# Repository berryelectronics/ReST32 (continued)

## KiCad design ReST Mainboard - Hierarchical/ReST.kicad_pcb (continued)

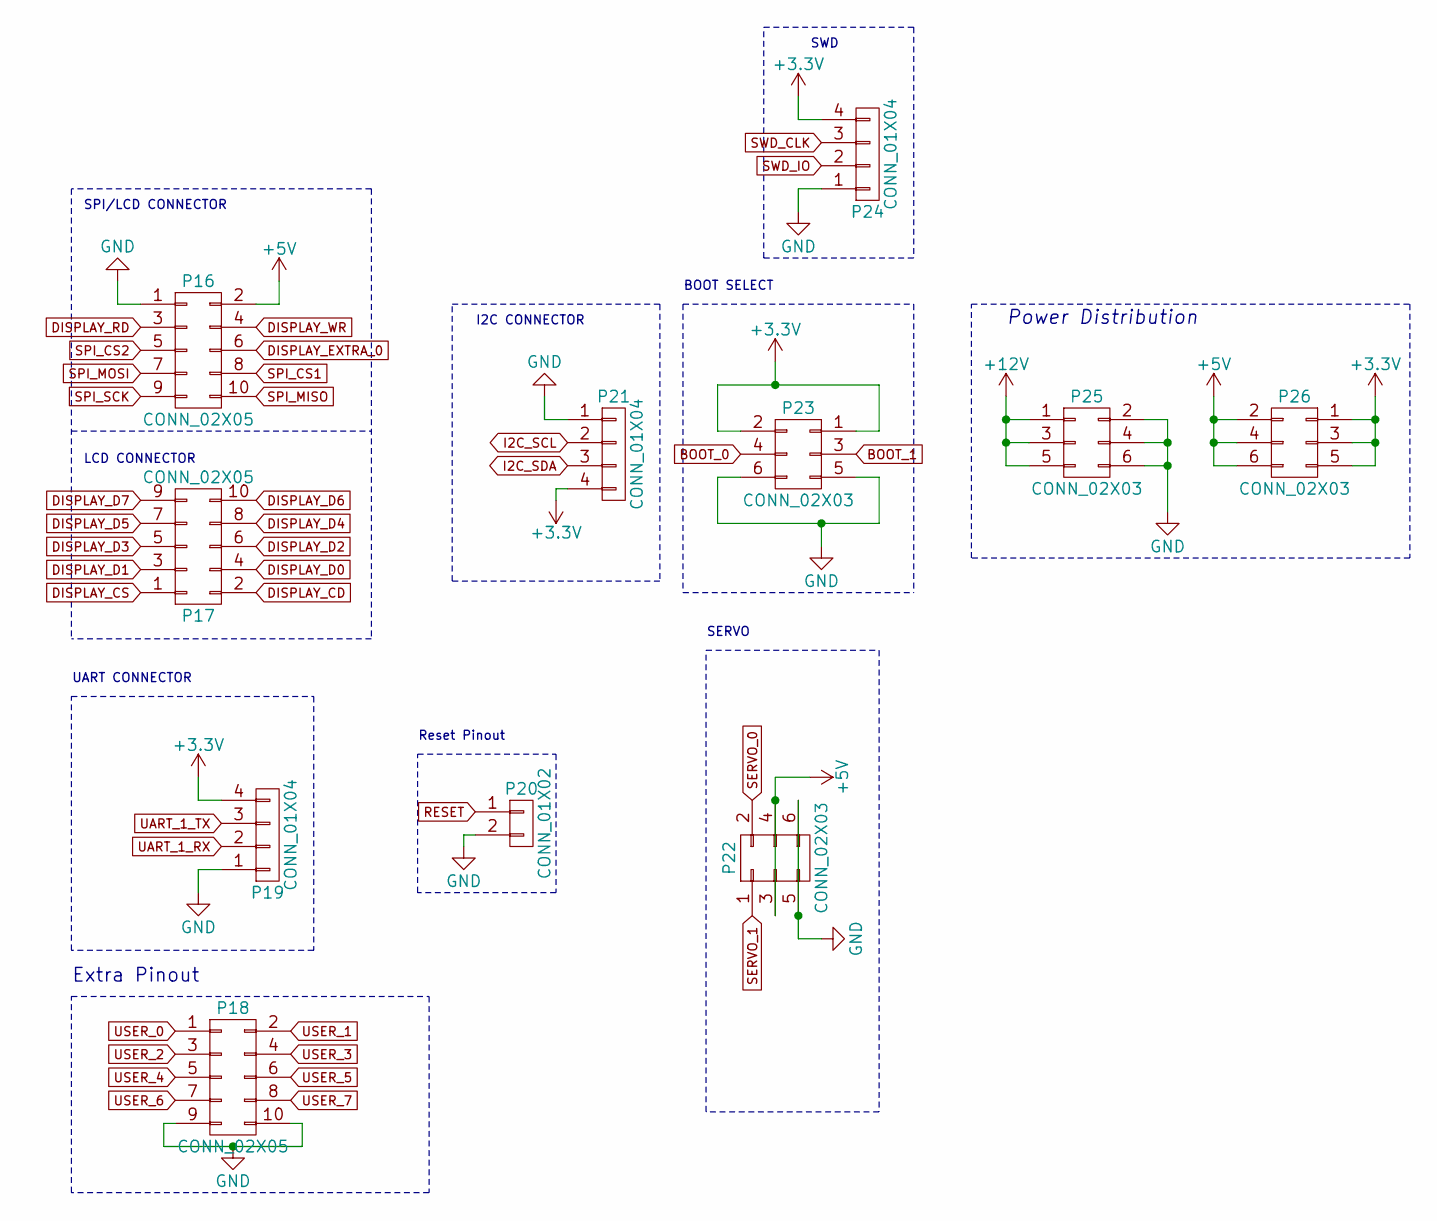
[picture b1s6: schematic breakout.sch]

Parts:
P16, P17: CONN_02X05; IDC_Header_Straight_10pins
P18: CONN_02X05; Pin_Header_Straight_2x05
P19, P24: CONN_01X04; bb02-hy04a
P20: CONN_01X02; Pin_Header_Straight_1x02
P21: CONN_01X04; Pin_Header_Straight_1x04
P22, P23: CONN_02X03; bb02-hp06
P25, P26: CONN_02X03; Pin_Header_Straight_2x03

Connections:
+5V: P16.2, P22.3, P22.4, P26.2, P26.4, P26.6; also elsewhere on the board
+12V: P25.1, P25.3, P25.5; also elsewhere on the board
BOOT_0: P23.4; also elsewhere on the board
BOOT_1: P23.3; also elsewhere on the board
DISPLAY_CD: P17.2; also elsewhere on the board
DISPLAY_CS: P17.1; also elsewhere on the board
DISPLAY_D0: P17.4; also elsewhere on the board
DISPLAY_D1: P17.3; also elsewhere on the board
DISPLAY_D2: P17.6; also elsewhere on the board
DISPLAY_D3: P17.5; also elsewhere on the board
DISPLAY_D4: P17.8; also elsewhere on the board
DISPLAY_D5: P17.7; also elsewhere on the board
DISPLAY_D6: P17.10; also elsewhere on the board
DISPLAY_D7: P17.9; also elsewhere on the board
DISPLAY_EXTRA_0: P16.6; also elsewhere on the board
DISPLAY_RD: P16.3; also elsewhere on the board
DISPLAY_WR: P16.4; also elsewhere on the board
GND: P16.1, P18.9, P18.10, P19.1, P20.2, P21.1, P22.5, P22.6, P23.5, P23.6, P24.1, P25.2, P25.4, P25.6; also elsewhere on the board
I2C_SCL: P21.2; also elsewhere on the board
I2C_SDA: P21.3; also elsewhere on the board
RESET: P20.1; also elsewhere on the board
SERVO_0: P22.2; also elsewhere on the board
SERVO_1: P22.1; also elsewhere on the board
SPI_CS1: P16.8; also elsewhere on the board
SPI_CS2: P16.5; also elsewhere on the board
SPI_MISO: P16.10; also elsewhere on the board
SPI_MOSI: P16.7; also elsewhere on the board
SPI_SCK: P16.9; also elsewhere on the board
SWD_CLK: P24.3; also elsewhere on the board
SWD_IO: P24.2; also elsewhere on the board
UART_1_RX: P19.2; also elsewhere on the board
UART_1_TX: P19.3; also elsewhere on the board
USER_0: P18.1; also elsewhere on the board
USER_1: P18.2; also elsewhere on the board
USER_2: P18.3; also elsewhere on the board
USER_3: P18.4; also elsewhere on the board
USER_4: P18.5; also elsewhere on the board
USER_5: P18.6; also elsewhere on the board
USER_6: P18.7; also elsewhere on the board
USER_7: P18.8; also elsewhere on the board

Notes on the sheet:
Power Distribution
SPI/LCD CONNECTOR
BOOT SELECT
I2C CONNECTOR
SERVO
UART CONNECTOR
SWD
LCD CONNECTOR
Extra Pinout
Reset Pinout

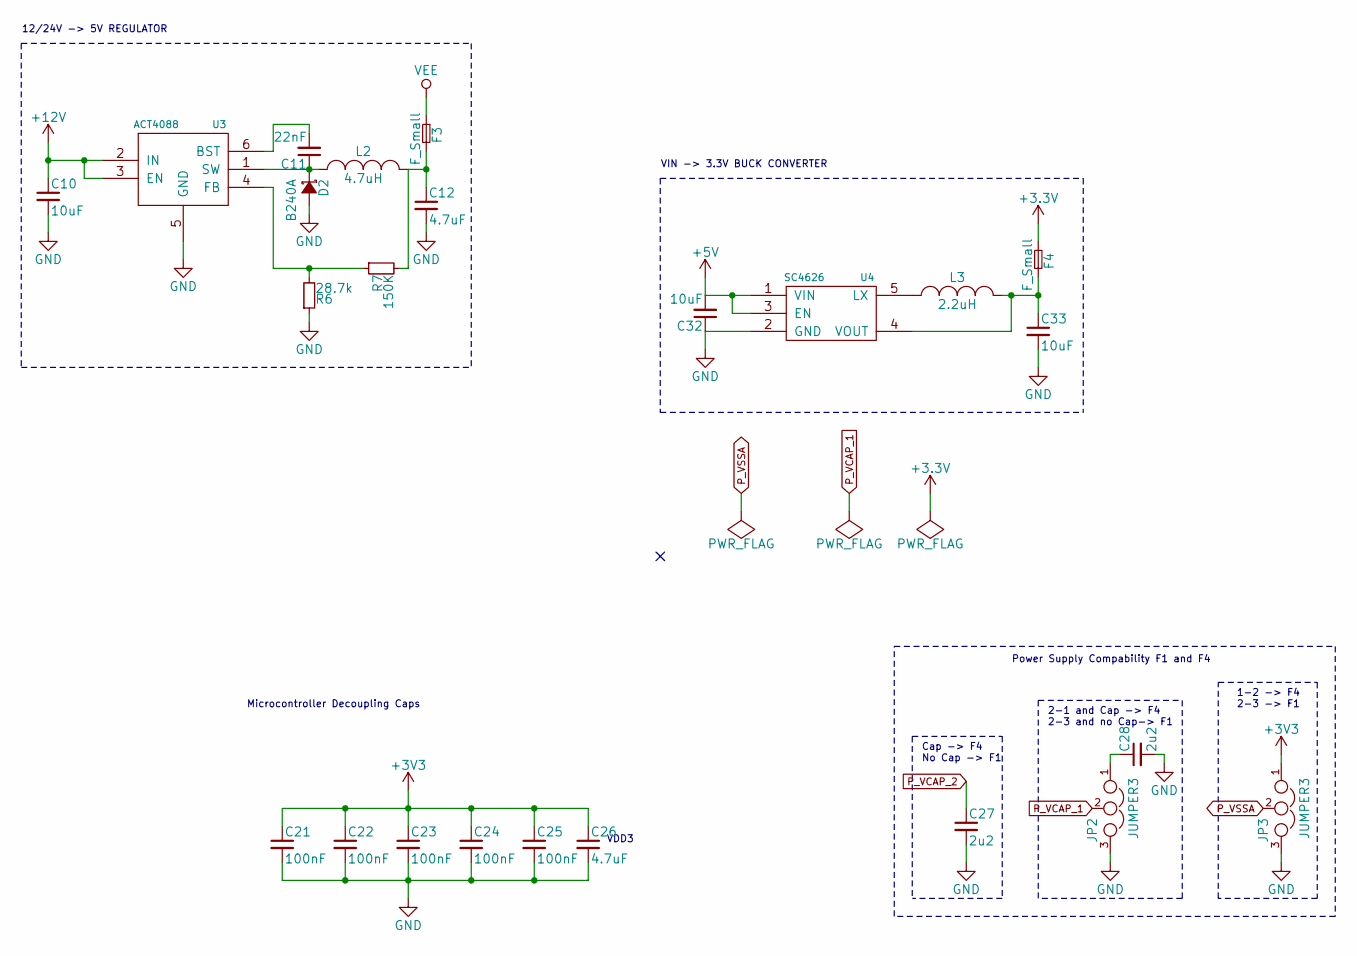
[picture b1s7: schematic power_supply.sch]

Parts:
C10: 10uF; C_1206_HandSoldering
C11: 22nF; C_0805_HandSoldering
C12, C26: 4.7uF; C_0805_HandSoldering
C21, C22, C23, C24, C25: 100nF; C_0805_HandSoldering
C27, C28: 2u2; C_0805_HandSoldering
C32, C33: 10uF; C_0805_HandSoldering
D2: B240A; DO-214AC.SMA
F3: F_Small; FUSE-1812
F4: F_Small; R_0805_HandSoldering
JP2, JP3: JUMPER3; S_JUMPER_3
L2: 4.7uH; CD32
L3: 2.2uH; CD32
R6: 28.7k; R_0805_HandSoldering
R7: 150K; R_0805_HandSoldering
U3: ACT4088; SOT-23-6
U4: SC4626; SOT-23-5

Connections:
+5V: C32.2, U4.1 (VIN), U4.3 (EN); also elsewhere on the board
+12V: C10.1, U3.2 (IN), U3.3 (EN); also elsewhere on the board
GND: C10.2, C12.2, C21.2, C22.2, C23.2, C24.2, C25.2, C26.2, C27.2, C28.2, C32.1, C33.2, D2.2 (A), JP2.3, JP3.3, R6.1, U3.5 (GND), U4.2 (GND); also elsewhere on the board
unnamed: C11.1, D2.1 (K), L2.1, U3.1 (SW)
unnamed: C11.2, U3.6 (BST)
unnamed: C12.1, F3.2, L2.2, R7.2
unnamed: C28.1, JP2.1
unnamed: C33.1, F4.2, L3.2, U4.4 (VOUT)
unnamed: L3.1, U4.5 (LX)
unnamed: R6.2, R7.1, U3.4 (FB)
P_VCAP_1: JP2.2; also elsewhere on the board
P_VCAP_2: C27.1; also elsewhere on the board
P_VSSA: JP3.2; also elsewhere on the board
VEE: F3.1; also elsewhere on the board

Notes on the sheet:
VIN -> 3.3V BUCK CONVERTER
12/24V -> 5V REGULATOR
2-1 and Cap -> F4 2-3 and no Cap-> F1
Cap -> F4 No Cap -> F1
1-2 -> F4 2-3 -> F1
Power Supply Compability F1 and F4
VDD3
Microcontroller Decoupling Caps

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
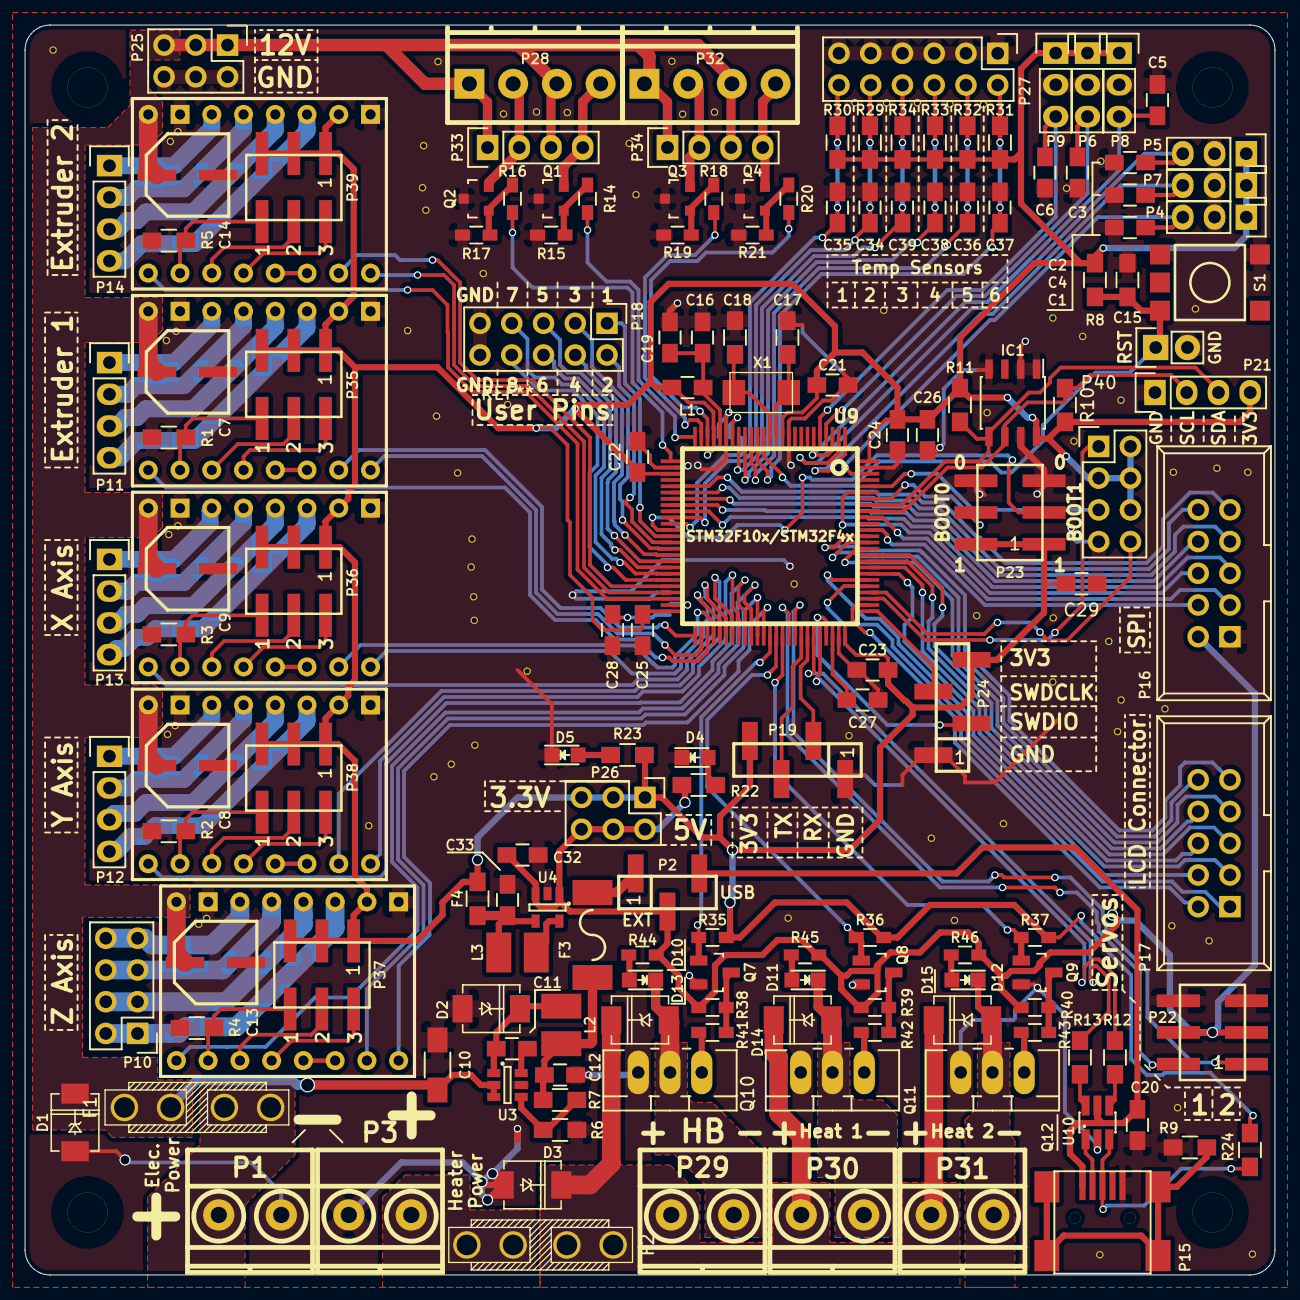
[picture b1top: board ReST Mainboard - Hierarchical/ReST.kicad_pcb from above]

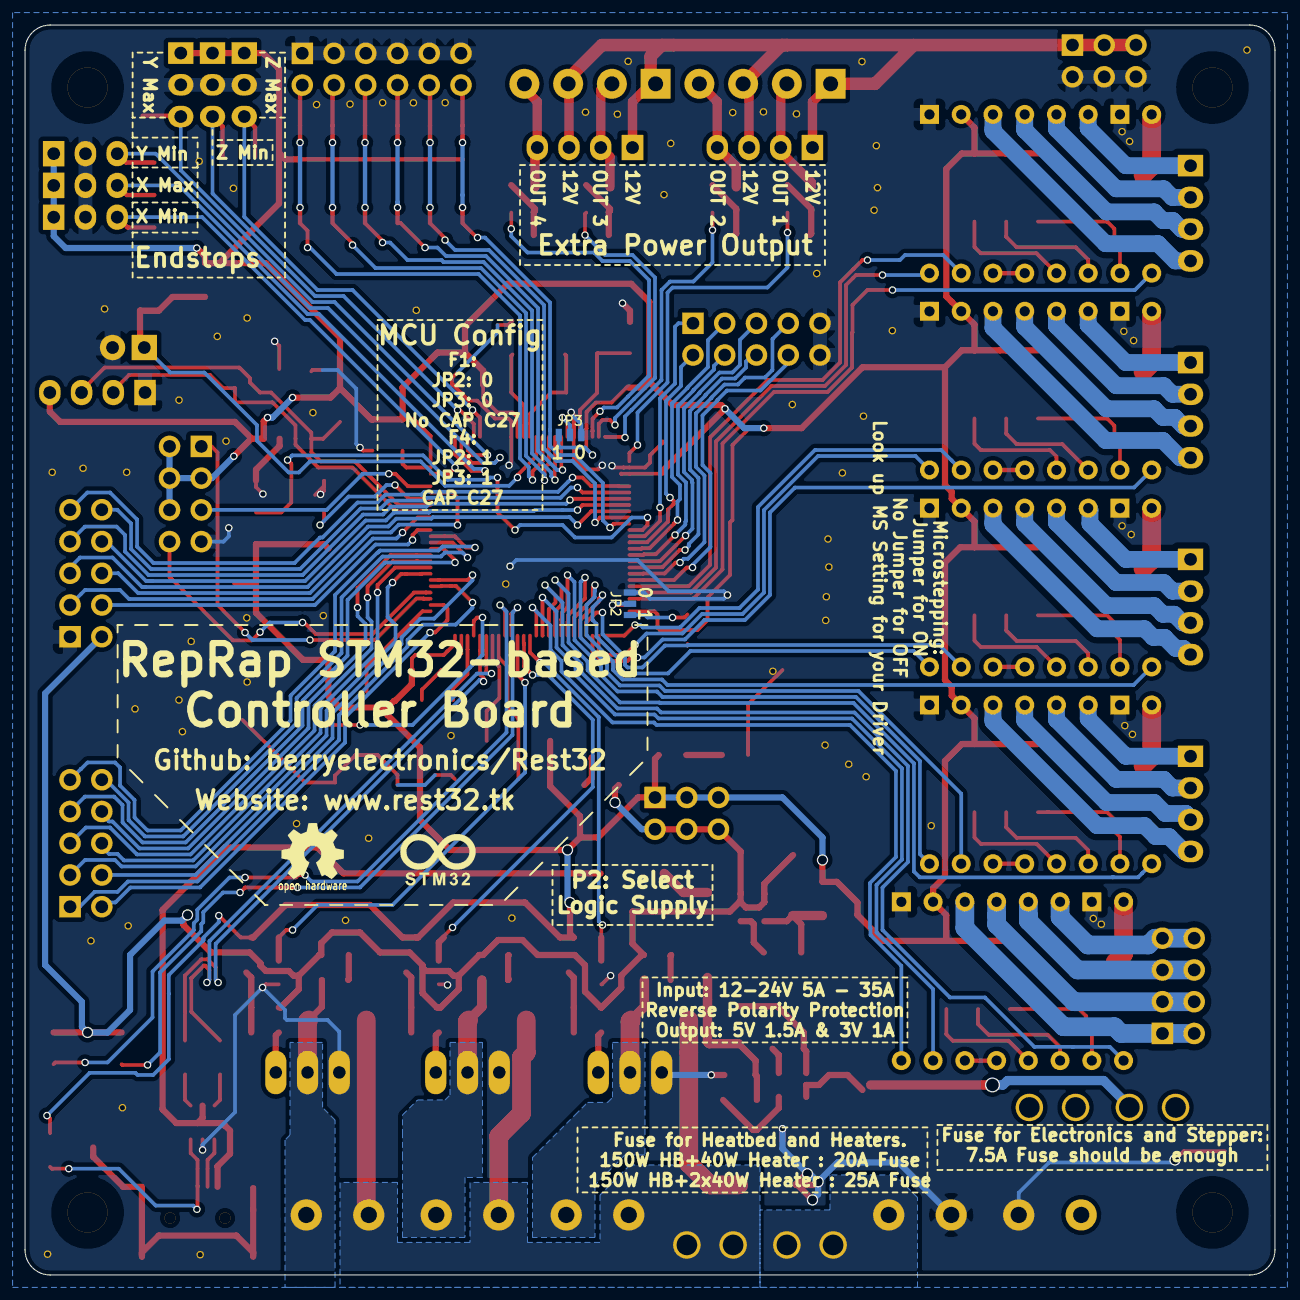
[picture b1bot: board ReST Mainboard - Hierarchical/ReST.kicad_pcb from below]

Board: 2 copper layers, 100.0 x 100.0 mm, 161 parts (2 on the bottom side), 165 nets.

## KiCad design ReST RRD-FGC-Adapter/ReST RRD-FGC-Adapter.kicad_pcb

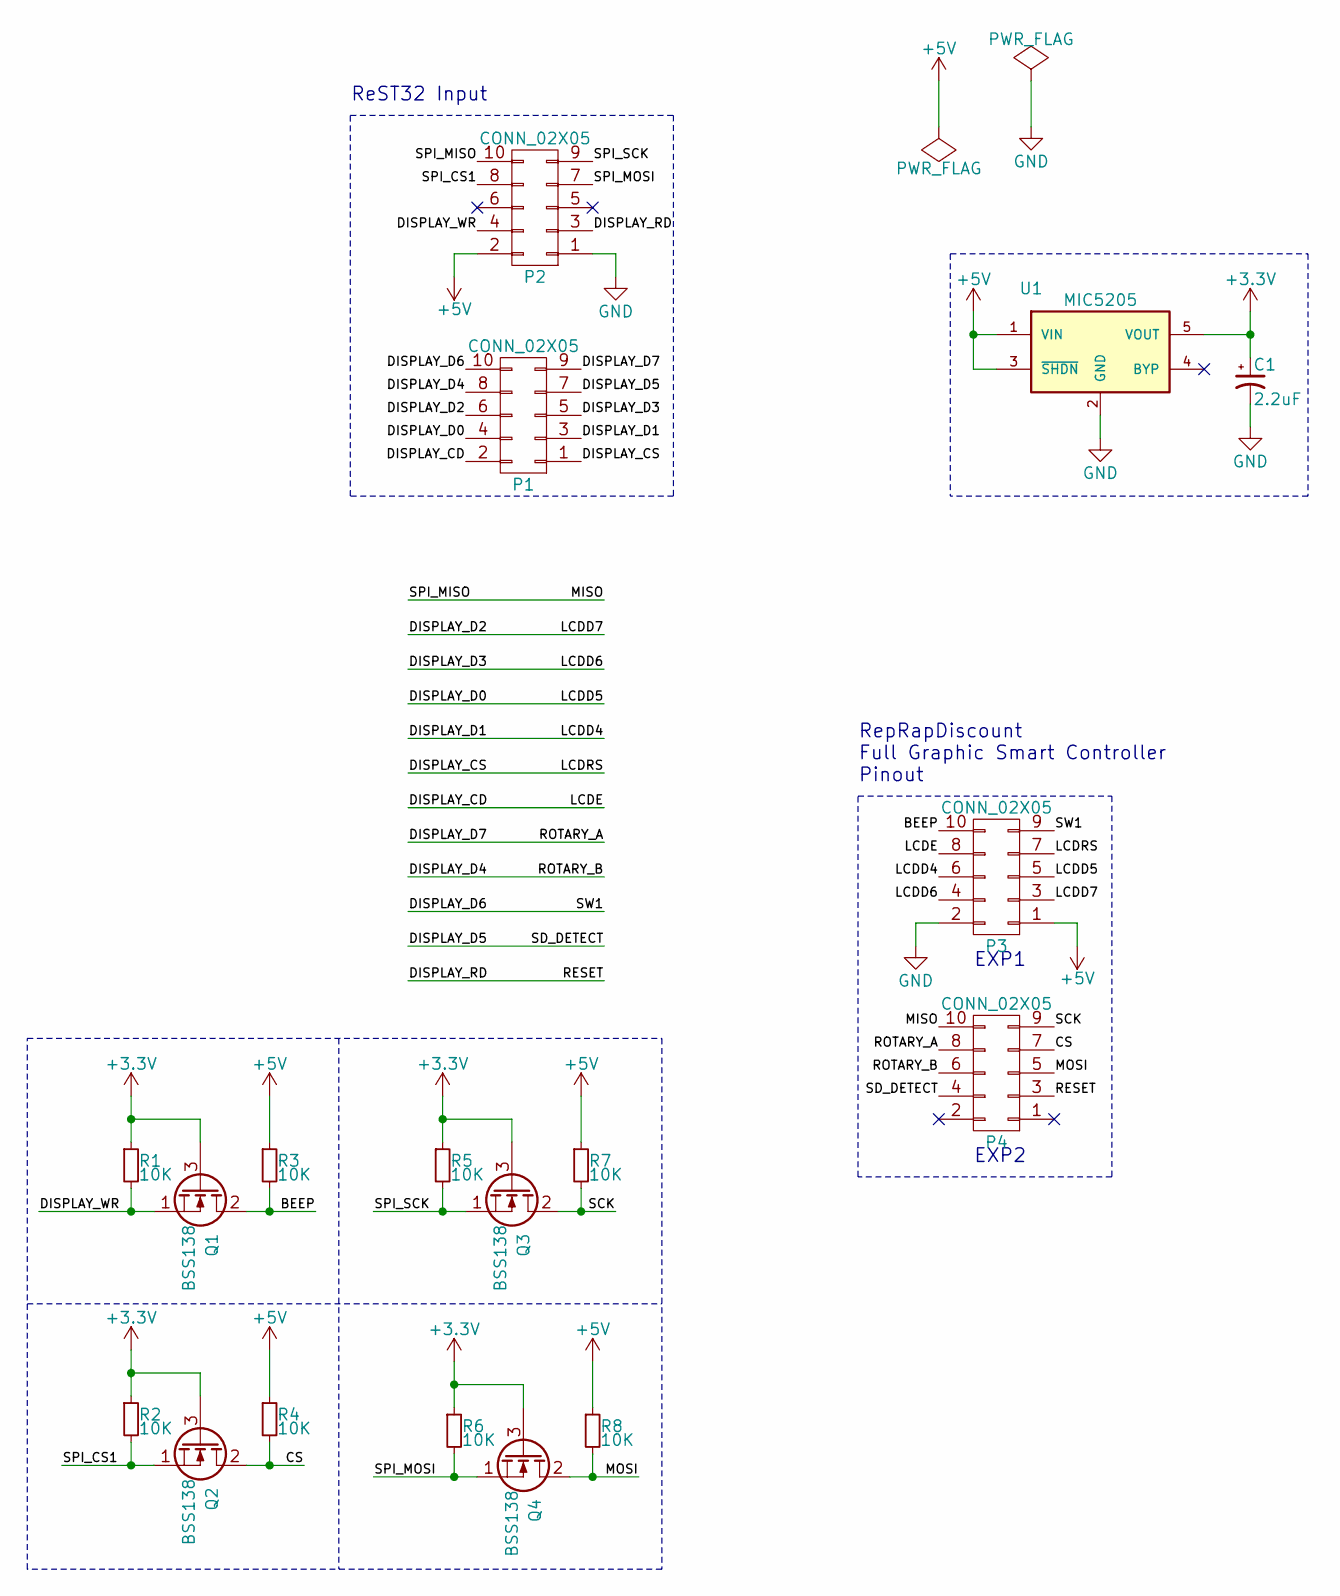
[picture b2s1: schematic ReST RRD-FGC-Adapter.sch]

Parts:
C1: 2.2uF; TantalC_SizeA_EIA-3216_HandSoldering
P1, P2: CONN_02X05; Pin_Header_Straight_2x05
P3, P4: CONN_02X05; IDC_Header_Straight_10pins
Q1, Q2, Q3, Q4: BSS138; SOT-23_Handsoldering
R1, R2, R3, R4, R5, R6, R7, R8: 10K; R_0805_HandSoldering
U1: MIC5205; SOT-23-5

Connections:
+3V3: C1.1, Q1.3 (G), Q2.3 (G), Q3.3 (G), Q4.3 (G), R1.1, R2.1, R5.1, R6.1, U1.5 (VOUT)
+5V: P2.2, P3.1, R3.1, R4.1, R7.1, R8.1, U1.1 (VIN), U1.3 (~SHDN~)
/BEEP: P3.10, Q1.2 (D), R3.2
/CS: P4.7, Q2.2 (D), R4.2
/DISPLAY_CD: P1.2, P3.8
/DISPLAY_CS: P1.1, P3.7
/DISPLAY_D0: P1.4, P3.5
/DISPLAY_D1: P1.3, P3.6
/DISPLAY_D2: P1.6, P3.3
/DISPLAY_D3: P1.5, P3.4
/DISPLAY_D4: P1.8, P4.6
/DISPLAY_D5: P1.7, P4.4
/DISPLAY_D6: P1.10, P3.9
/DISPLAY_D7: P1.9, P4.8
/DISPLAY_RD: P2.3, P4.3
/DISPLAY_WR: P2.4, Q1.1 (S), R1.2
/MISO: P2.10, P4.10
/MOSI: P4.5, Q4.2 (D), R8.2
/SCK: P4.9, Q3.2 (D), R7.2
/SPI_CS1: P2.8, Q2.1 (S), R2.2
/SPI_MOSI: P2.7, Q4.1 (S), R6.2
/SPI_SCK: P2.9, Q3.1 (S), R5.2
GND: C1.2, P2.1, P3.2, U1.2 (GND)

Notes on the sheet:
ReST32 Input
EXP1
EXP2
RepRapDiscount Full Graphic Smart Controller Pinout

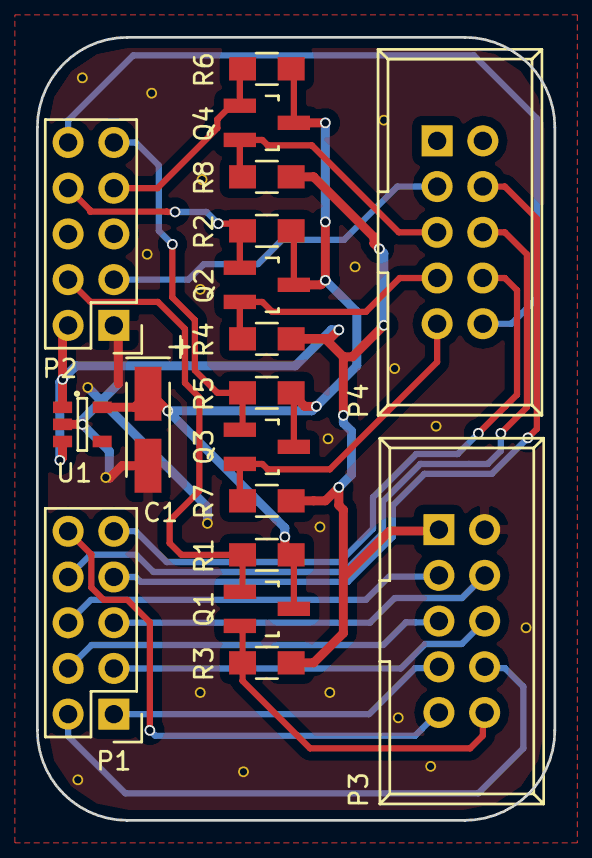
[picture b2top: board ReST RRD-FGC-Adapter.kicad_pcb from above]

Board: 2 copper layers, 28.8 x 43.5 mm, 18 parts (0 on the bottom side), 23 nets.

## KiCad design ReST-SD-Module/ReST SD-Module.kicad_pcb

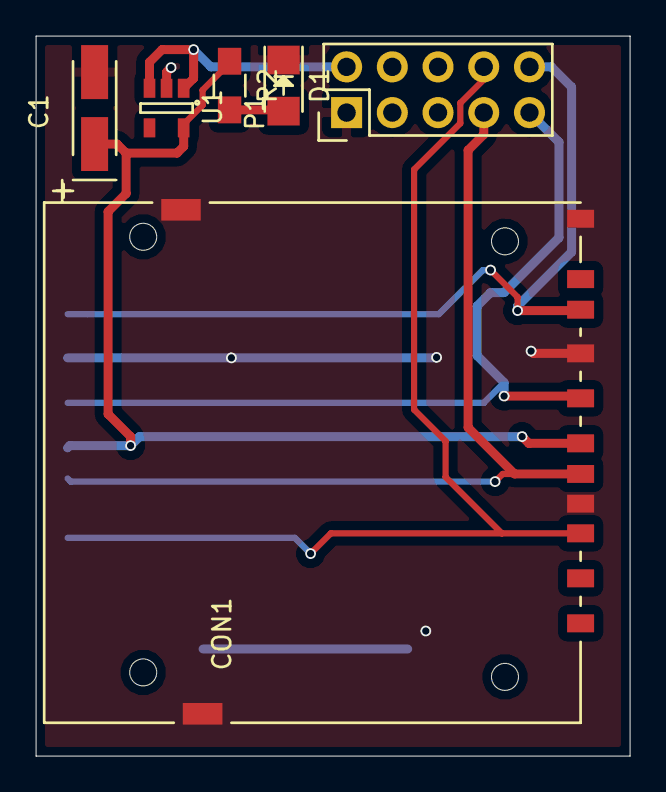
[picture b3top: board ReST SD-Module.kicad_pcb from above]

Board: 2 copper layers, 33.0 x 40.0 mm, 7 parts (1 on the bottom side), 8 nets.

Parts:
C1: CP1_Small; TantalC_SizeA_EIA-3216_HandSoldering
CON1, CON2: uSD_Card; SD_Card_Receptacle
D1: Led_Small; LED_1206
P1: CONN_02X05; Pin_Header_Straight_2x05
R2: 1K; R_0805_HandSoldering
U1: MIC5205; SOT-23-5

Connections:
+3V3: C1.1, CON1.4, CON2.4, R2.1, U1.5
+5V: P1.2, U1.1, U1.3
/SPI-CS: CON1.2, CON2.2, P1.8
/SPI-MISO: CON1.7, CON2.7, P1.10
/SPI-MOSI: CON1.3, CON2.3, P1.7
/SPI-SCK: CON1.5, CON2.5, P1.9
GND: C1.2, CON1.6, CON1.10, CON1.11, CON1.12, CON1.13, CON2.6, CON2.10, CON2.11, CON2.12, CON2.13, D1.1, P1.1, U1.2
unnamed: D1.2, R2.2

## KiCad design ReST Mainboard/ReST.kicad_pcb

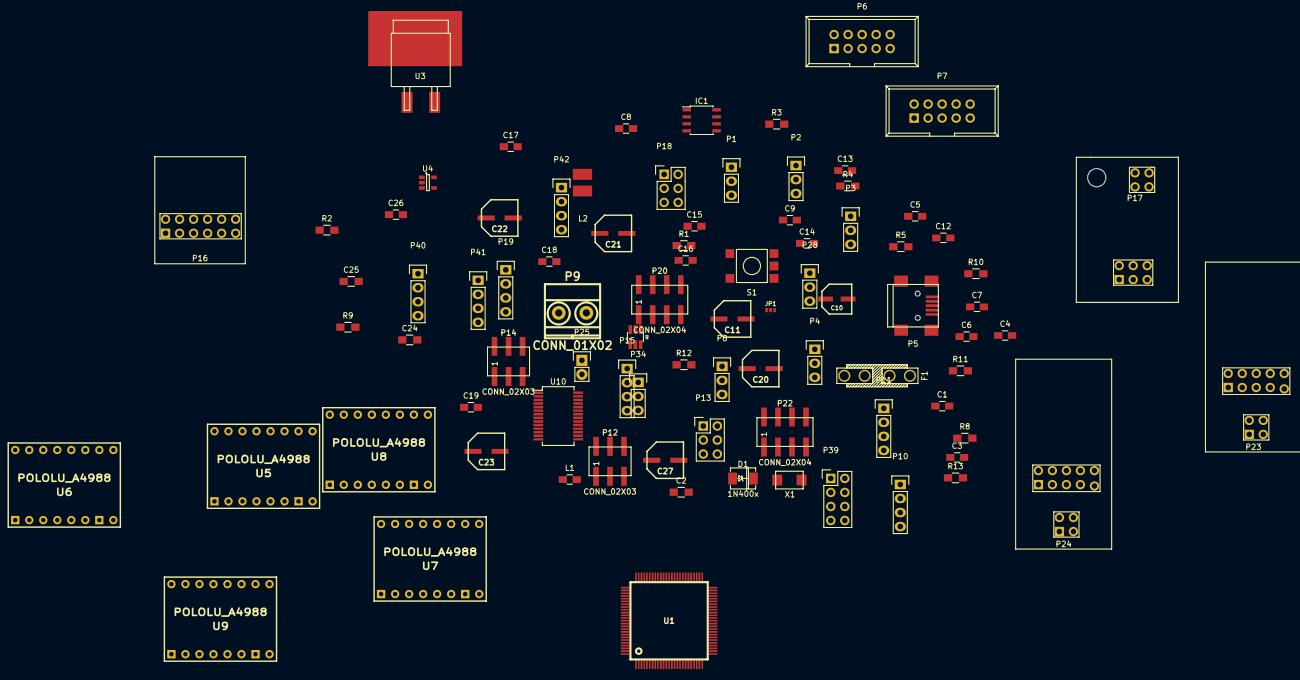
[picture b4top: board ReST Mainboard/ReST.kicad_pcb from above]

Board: 2 copper layers, 86 parts (0 on the bottom side), 127 nets, no tracks yet.

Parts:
C1, C3, C4, C5, C6, C7, C9: 100nF; C_0805_HandSoldering
C2: 100nF; R_0805_HandSoldering
C8, C12, C13: 10uF; C_0805_HandSoldering
C10: 10uF; CP-PANASONIC-SMT_C
C11: 22uF; CP-PANASONIC-SMT_D
C14, C15, C16, C17, C18, C19: 10nF; C_0805_HandSoldering
C20, C21, C22, C23, C27: 100uF; CP-PANASONIC-SMT_D8
C24, C25: 30pF; R_0805_HandSoldering
C26: 4.7uF; C_0805_HandSoldering
D1: 1N400x; DO-214AC.SMA
F1: F_Small; MINI-FUSE
IC1: AT24C128; SOIC-8_3.9x4.9mm_Pitch1.27mm
JP1: JUMPER3; S_JUMPER_3
L1: BEAD; C_0805_HandSoldering
L2: 2.2uH; CD32
P1, P2, P3, P4, P8, P28, P34: CONN_01X03; Pin_Header_Straight_1x03
P5: USB_OTG; USB_Mini-B
P6, P7: CONN_02X05; IDC_Header_Straight_10pins
P9: CONN_01X02; screw-5-2P
P10, P11, P15, P19, P40, P41, P42: CONN_01X04; Pin_Header_Straight_1x04
P12, P14: CONN_02X03; bb02-hp06
P13, P18: CONN_02X03; Pin_Header_Straight_2x03
P16: CONN_02X06; REST_ADDITIONAL
P17: CONN_02X03; REST_HEATBED
P20, P22: CONN_02X04; bb02-hp08
P23, P24: CONN_02X07; REST_HEATER
P25: CONN_01X02; Pin_Header_Straight_1x02
P39: CONN_02X04; Pin_Header_Straight_2x04
R1: 1M; R_0805_HandSoldering
R2, R3: 22R; R_0805_HandSoldering
R4, R8, R9, R10, R11: 100K; R_0805_HandSoldering
R5: 10K; R_0805_HandSoldering
R12, R13: 4K7; R_0805_HandSoldering
S1: SW_DIP_x2; SMD-BUTTON-6MM
U1: STM32F10x/STM32F4x; LQFP100-14x14
U2: USBLC6-2; SOT32-6L
U3: L7805ACD2T-TR; SOT-404
U4: LM3671MFX-3.3; SOT-23-5
U5, U6, U7, U8, U9: POLOLU_A4988; SWDIP8_.6W
U10: MCP23017; SSOP-28_5.3x10.2mm_Pitch0.65mm
X1: Crystal_Small; 2P-5032

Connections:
+3V3: C1.1, C3.1, C4.1, C5.1, C6.1, C13.2, C26.1, IC1.8, JP1.1, L1.1, L2.2, P1.1, P2.1, P3.1, P4.1, P10.4, P11.4, P14.1, P14.2, P17.2, P18.2, P18.4, P18.6, P19.4, P23.1, P24.1, P28.1, P34.1, R5.2, R12.2, R13.2, U1.11, U1.22, U1.28, U1.50, U1.75, U1.100, U4.4, U5.2, U6.2, U7.2, U8.2, U9.2, U10.9, U10.16, U10.17
+5V: C12.2, P6.2, P8.2, P12.3, P12.4, P17.1, P18.1, P18.3, P18.5, P23.2, P24.2, U4.1, U4.3
+12V: C10.1, C20.1, C21.1, C22.1, C23.1, C27.1, D1.1, F1.2, P13.1, P13.3, P13.5, P16.6, P16.8, P16.10, P16.12, P23.5, P23.6, P23.7, P23.8, P23.9, P24.5, P24.6, P24.7, P24.8, P24.9, U3.1, U5.8, U6.8, U7.8, U8.8, U9.8
/12V-RAW: F1.1, P9.2
/BOOT0: P14.3, U1.94
/BOOT1: P14.4, U1.37
/E0-DIR: U1.24, U5.16
/E0-EN: U1.18, U5.9
/E0-STEP: U1.23, U5.15
/E0M1: R8.1, U5.10, U10.24
/E0M2: U5.11, U10.23
/E0M3: U5.12, U10.22
/E0RST: U1.97, U5.13, U5.14
/E1-DIR: U1.87, U9.16
/E1-EN: U1.91, U9.9
/E1-STEP: U1.88, U9.15
/E1M1: R4.1, U9.10, U10.27
/E1M2: U9.11, U10.26
/E1M3: U9.12, U10.25
/E1RST: U1.98, U9.13, U9.14
/I2C-SCL: IC1.6, P10.2, R13.1, U1.92, U10.12
/I2C-SDA: IC1.5, P10.3, R12.1, U1.93, U10.13
/IO1: P20.1, U1.2
/IO2: P20.2, U1.1
/IO5: P20.5, U1.96
/IO7: P22.1, U1.67
/IO8: P22.2, U1.66
/IO9: P22.3, U1.62
/IO10: P22.4, U1.61
/IO11: P22.5, U1.60
/IO12: P22.6, U1.59
/LCD-CD: P7.9, U1.47
/LCD-CS: P7.10, U1.46
/LCD-D0: P7.2, U1.38
/LCD-D1: P7.1, U1.39
/LCD-D2: P7.4, U1.40
/LCD-D3: P7.3, U1.41
/LCD-D4: P7.6, U1.42
/LCD-D5: P7.5, U1.43
/LCD-D6: P7.8, U1.44
/LCD-D7: P7.7, U1.45
/LCD-RD: P6.10, U1.56
/LCD-WR: P6.9, U1.48
/LCD_PWM: P6.4, U1.95
/PWM-ADD0: P16.11, U1.36
/PWM-ADD1: P16.9, U1.63
/PWM-ADD2: P16.7, U1.64
/PWM-ADD3: P16.5, U1.65
/PWM-BED: P17.4, U1.31
/PWM-HEAT0: P24.4, U1.32
/PWM-HEAT1: P23.4, U1.30
/RESET: C2.2, P25.1, R5.1, S1.1, S1.2, U1.14
/SERVO1: P12.1, U1.57
/SERVO2: P12.2, U1.58
/SPI-CS1: P6.6, U1.51
/SPI-CS2: P6.8, U1.55
/SPI-MISO: P6.5, U1.53
/SPI-MOSI: P6.7, U1.54
/SPI-SCK: P6.3, U1.52
/SWCLK: P19.3, U1.76
/SWDIO: P19.2, U1.72
/T0: P17.6, U1.33
/T1: P24.3, U1.34
/T2: P23.3, U1.35
/UART1-RX: P11.2, U1.69
/UART1-TX: P11.3, U1.68
/USB+: R2.2, U1.71
/USB-: R3.1, U1.70
/USBR+: R2.1, U2.4
/USBR-: R3.2, U2.6
/USB_D+: P5.3, U2.3
/USB_D-: P5.2, U2.1
/X-DIR: U1.29, U8.16
/X-EN: U1.25, U8.9
/X-MAX: C17.1, P3.3, U1.79
/X-MIN: C14.1, P1.3, U1.78
/X-STEP: U1.26, U8.15
/XM1: R10.1, U8.10, U10.3
/XM2: U8.11, U10.2
/XM3: U8.12, U10.1
/XRST: U1.84, U8.13, U8.14
/Y-DIR: U1.15, U6.16
/Y-EN: U1.17, U6.9
/Y-MAX: C18.1, P4.3, U1.81
/Y-MIN: C15.1, P2.3, U1.80
/Y-STEP: U1.16, U6.15
/YM1: R9.1, U6.10, U10.6
/YM2: U6.11, U10.5
/YM3: U6.12, U10.4
/YRST: U1.85, U6.13, U6.14
/Z-DIR: U1.3, U7.16
/Z-EN: U1.5, U7.9
/Z-MAX: C19.1, P34.3, U1.83
/Z-MIN: C16.1, P28.3, U1.82
/Z-STEP: U1.4, U7.15
/ZM1: R11.1, U7.10, U10.21
/ZM2: U7.11, U10.8
/ZM3: U7.12, U10.7
/ZRST: U1.86, U7.13, U7.14
GND: C1.2, C2.1, C3.2, C4.2, C5.2, C6.2, C7.2, C8.2, C9.2, C10.2, C11.2, C12.1, C13.1, C14.2, C15.2, C16.2, C17.2, C18.2, C19.2, C20.2, C21.2, C22.2, C23.2, C24.1, C25.2, C26.2, C27.2, D1.2, IC1.1, IC1.2, IC1.4, IC1.7, JP1.2, JP1.3, P1.2, P2.2, P3.2, P4.2, P5.5, P6.1, P9.1, P10.1, P11.1, P12.5, P12.6, P13.2, P13.4, P13.6, P14.5, P14.6, P16.1, P16.2, P16.3, P16.4, P17.3, P17.5, P19.1, P20.7, P20.8, P22.7, P22.8, P23.10, P23.11, P23.12, P23.13, P23.14, P24.10, P24.11, P24.12, P24.13, P24.14, P25.2, P28.2, P34.2, R1.1, R4.2, R8.2, R9.2, R10.2, R11.2, S1.3, S1.4, U1.10, U1.19, U1.20, U1.27, U1.49, U1.74, U1.99, U2.2, U3.2, U4.2, U5.1, U5.7, U6.1, U6.7, U7.1, U7.7, U8.1, U8.7, U9.1, U9.7, U10.10, U10.15
unnamed: C8.1, C9.1, L1.2, U1.21
unnamed: C24.2, U1.12, X1.2
unnamed: C25.1, U1.13, X1.1
unnamed: L2.1, U4.5
unnamed: P5.6, R1.2
unnamed: P15.1, U9.6
unnamed: P15.2, U9.5
unnamed: P15.3, U9.4
unnamed: P15.4, U9.3
unnamed: P39.1, P39.2, U7.3
unnamed: P39.3, P39.4, U7.4
unnamed: P39.5, P39.6, U7.5
unnamed: P39.7, P39.8, U7.6
unnamed: P40.1, U5.6
unnamed: P40.2, U5.5
unnamed: P40.3, U5.4
unnamed: P40.4, U5.3
unnamed: P41.1, U6.6
unnamed: P41.2, U6.5
unnamed: P41.3, U6.4
unnamed: P41.4, U6.3
unnamed: P42.1, U8.6
unnamed: P42.2, U8.5
unnamed: P42.3, U8.4
unnamed: P42.4, U8.3
VCC: C7.1, P5.1, P8.1, U2.5
VEE: C11.1, P8.3, U3.3

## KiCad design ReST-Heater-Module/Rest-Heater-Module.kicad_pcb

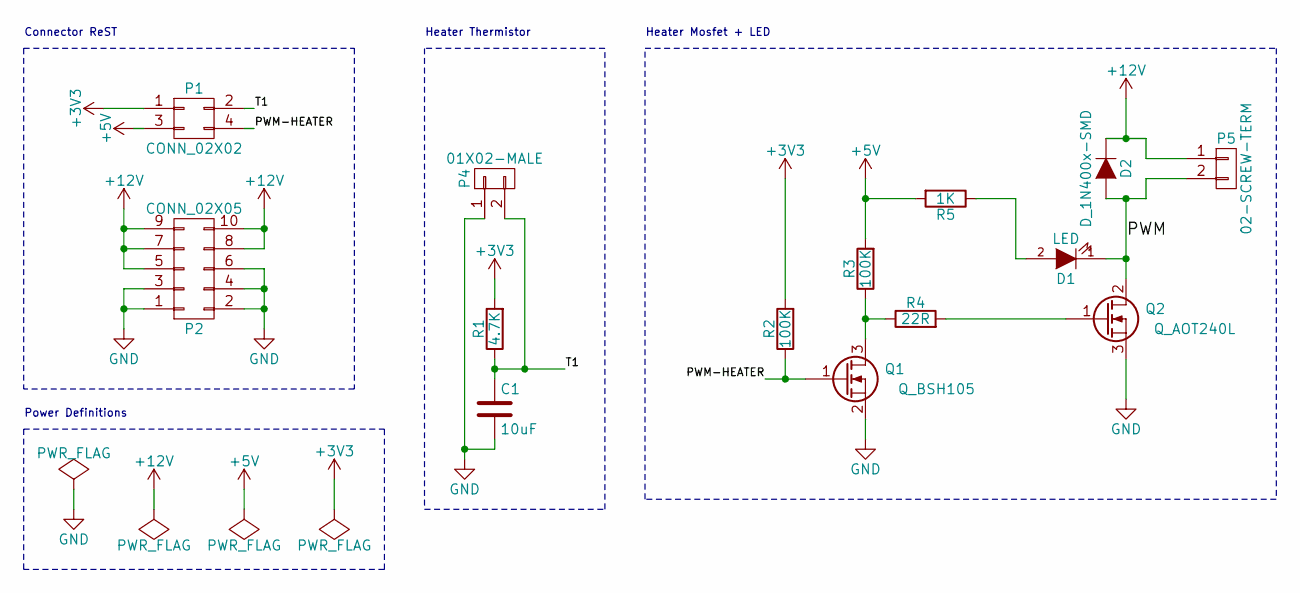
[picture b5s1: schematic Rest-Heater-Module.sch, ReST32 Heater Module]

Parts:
C1: 10uF; C_0805_HandSoldering
D1: LED; LED_1206
D2: D_1N400x-SMD; DO-214AC.SMA
P1: CONN_02X02; bb02-hp04
P2: CONN_02X05; bb02-hp10
P4: 01X02-MALE; bb02-hy02a
P5: 02-SCREW-TERM; screw-5-2P
Q1: Q_BSH105; SOT-23
Q2: Q_AOT240L; TO-220_Neutral123_Vertical_LargePads
R1: 4.7K; R_0603_HandSoldering
R2, R3: 100K; R_0603_HandSoldering
R4: 22R; R_0603_HandSoldering
R5: 1K; R_0603_HandSoldering

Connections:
+3V3: P1.1, R1.2, R2.2
+5V: P1.3, R3.2, R5.2
+12V: D2.1 (K), P2.5, P2.7, P2.8, P2.9, P2.10, P5.1
/PWM: D1.1 (K), D2.2 (A), P5.2, Q2.2 (D)
/PWM-HEATER: P1.4, Q1.1 (G), R2.1
/T1: C1.1, P1.2, P4.2, R1.1
GND: C1.2, P2.1, P2.2, P2.3, P2.4, P2.6, P4.1, Q1.2 (S), Q2.3 (S)
unnamed: D1.2 (A), R5.1
unnamed: Q1.3 (D), R3.1, R4.1
unnamed: Q2.1 (G), R4.2

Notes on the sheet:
Heater Mosfet + LED
Heater Thermistor
Connector ReST
Power Definitions

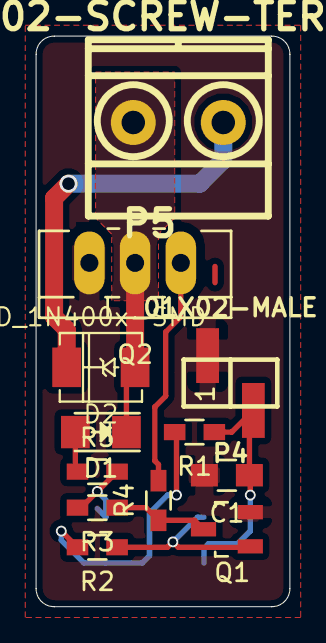
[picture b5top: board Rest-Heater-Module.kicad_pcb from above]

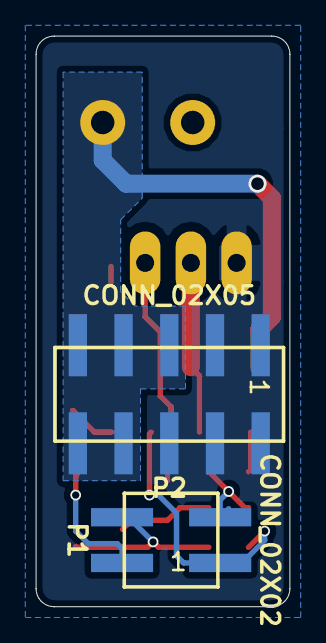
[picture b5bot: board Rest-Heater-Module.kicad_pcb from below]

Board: 2 copper layers, 14.1 x 31.7 mm, 14 parts (2 on the bottom side), 10 nets.

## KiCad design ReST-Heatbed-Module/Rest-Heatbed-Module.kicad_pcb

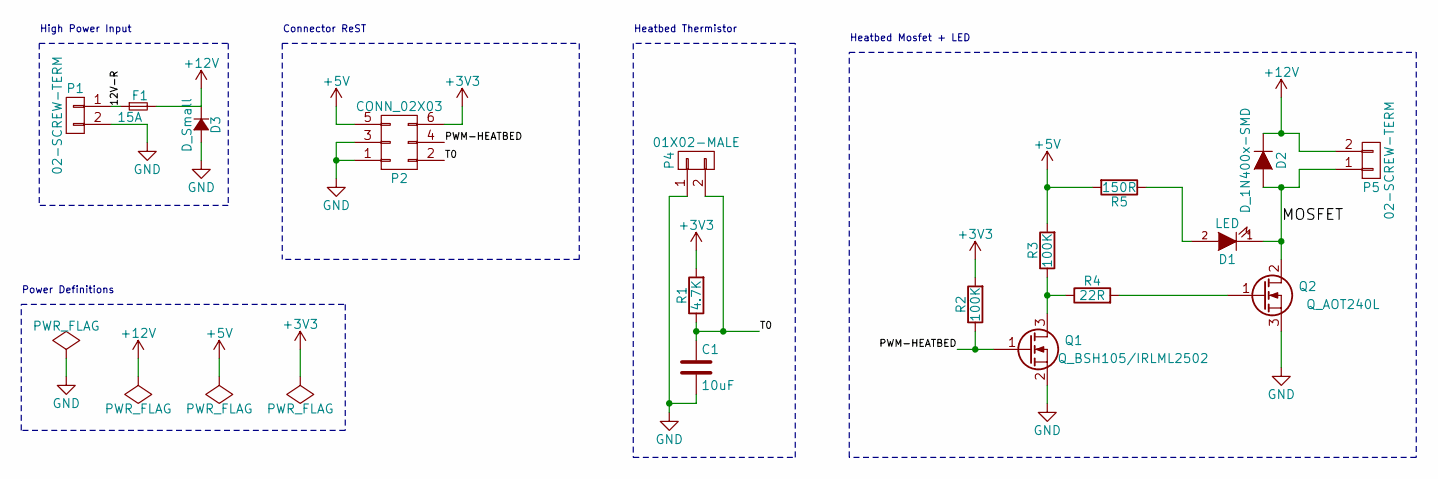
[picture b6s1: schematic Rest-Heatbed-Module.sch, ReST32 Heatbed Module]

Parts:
C1: 10uF; C_0805_HandSoldering
D1: LED; LED_0805
D2: D_1N400x-SMD; DO-214AC.SMA
D3: D_Small; DO-214AC.SMA
F1: 15A; MINI-FUSE
P1, P5: 02-SCREW-TERM; screw-5-2P
P2: CONN_02X03; bb02-hp06
P4: 01X02-MALE; bb02-hy02a
Q1: Q_BSH105/IRLML2502; SOT-23
Q2: Q_AOT240L; TO-220_Neutral123_Vertical_LargePads_Heatsink
R1: 4.7K; R_0603_HandSoldering
R2, R3: 100K; R_0603_HandSoldering
R4: 22R; R_0603_HandSoldering
R5: 150R; R_0603_HandSoldering

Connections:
+3V3: P2.6, R1.2, R2.2
+5V: P2.5, R3.2, R5.2
+12V: D2.1 (K), D3.1 (K), F1.2, P5.2
/12V-R: F1.1, P1.1
/MOSFET: D1.1 (K), D2.2 (A), P5.1, Q2.2 (D)
/PWM-HEATBED: P2.4, Q1.1 (G), R2.1
/T0: C1.1, P2.2, P4.2, R1.1
GND: C1.2, D3.2 (A), P1.2, P2.1, P2.3, P4.1, Q1.2 (S), Q2.3 (S)
unnamed: D1.2 (A), R5.1
unnamed: Q1.3 (D), R3.1, R4.1
unnamed: Q2.1 (G), R4.2

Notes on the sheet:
Heatbed Mosfet + LED
Heatbed Thermistor
High Power Input
Connector ReST
Power Definitions

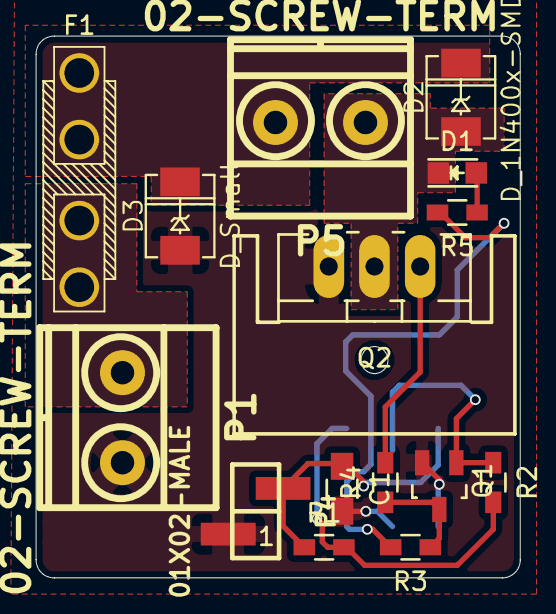
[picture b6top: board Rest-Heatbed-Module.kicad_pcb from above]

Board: 2 copper layers, 26.9 x 30.1 mm, 16 parts (1 on the bottom side), 11 nets.

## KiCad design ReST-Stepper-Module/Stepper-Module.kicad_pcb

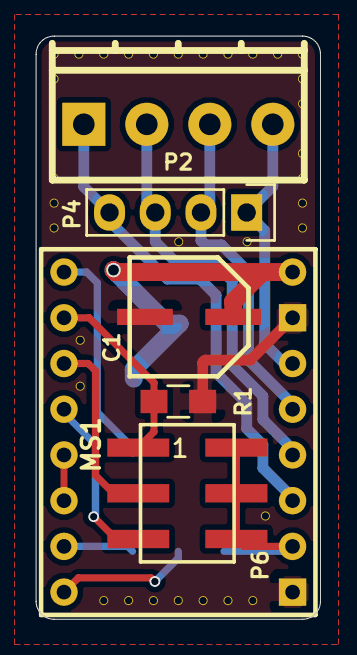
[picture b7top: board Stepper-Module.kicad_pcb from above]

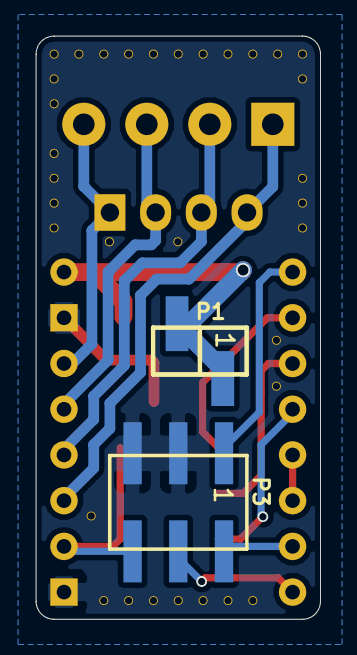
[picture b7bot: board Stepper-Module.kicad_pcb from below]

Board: 2 copper layers, 15.8 x 32.4 mm, 7 parts (2 on the bottom side), 8 nets.

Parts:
C1: CP-PANASONIC-SMT_D8
P1: bb02-hy02a
P2: pt_1,5-4-3,5-h
P3, P6: bb02-hp06
P4: Pin_Header_Straight_1x04
R1: R_0805_HandSoldering

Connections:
+3V3: P3.6, P6.2, P6.4, P6.6
+12V: C1.1, P1.1, P1.2
GND: C1.2, P3.3, P3.5, R1.2
unnamed: P2.1, P4.4
unnamed: P2.2, P4.3
unnamed: P2.3, P4.2
unnamed: P2.4, P4.1
unnamed: P6.1, R1.1
